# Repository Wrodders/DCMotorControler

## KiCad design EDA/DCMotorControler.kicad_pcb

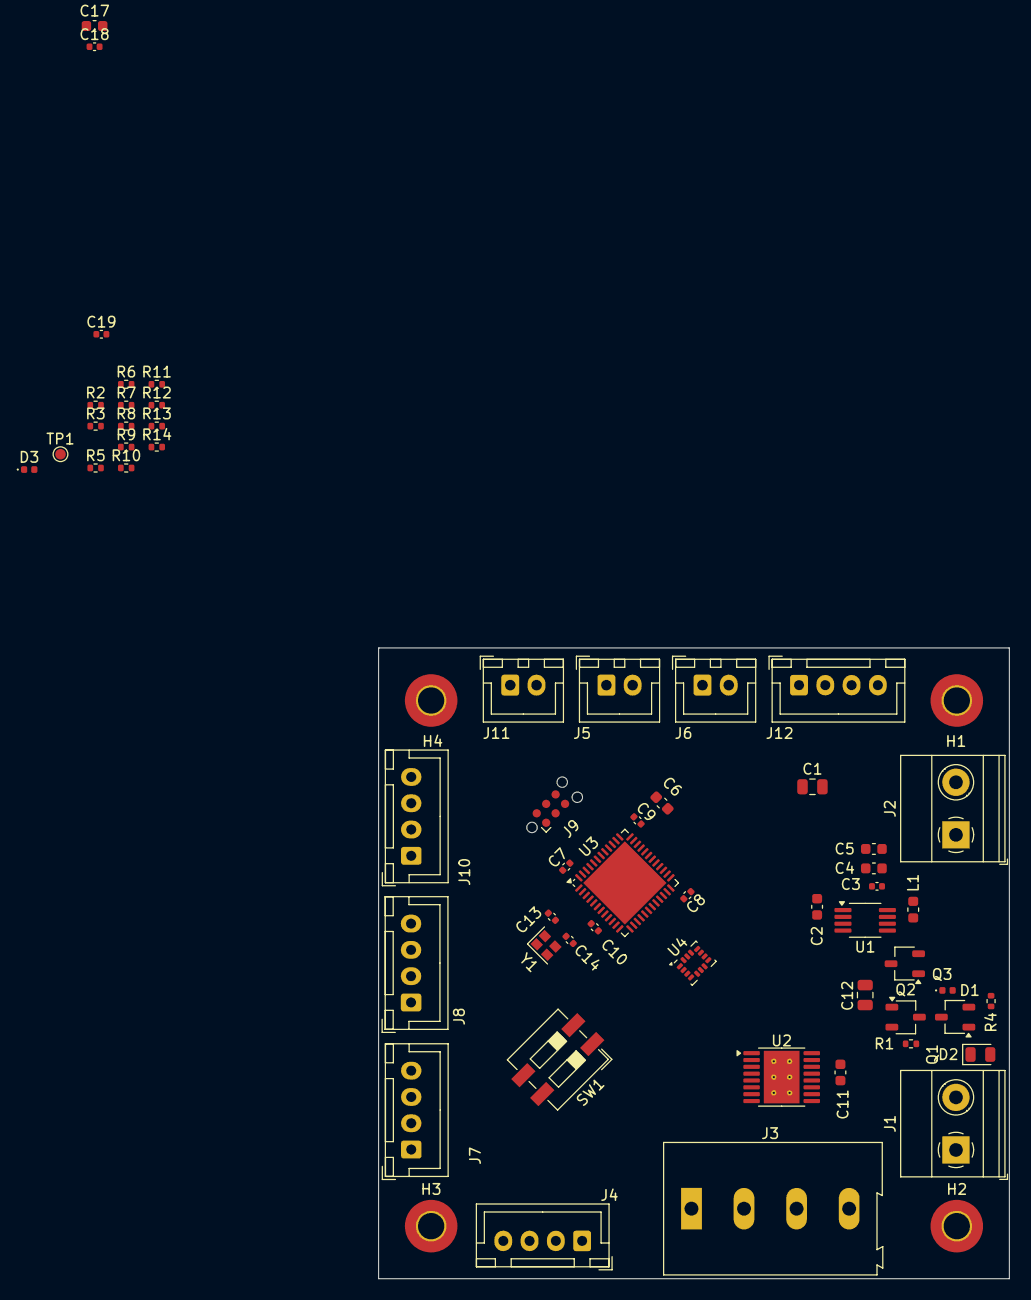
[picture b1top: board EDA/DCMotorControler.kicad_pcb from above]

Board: 2 copper layers, 60.0 x 60.0 mm, 61 parts (0 on the bottom side), 58 nets, no tracks yet.

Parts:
C1, C12: 47u; C_0805_2012Metric
C2, C4, C5, C11: 10u; C_0603_1608Metric
C3, C7, C8, C9, C10: 100n; C_0402_1005Metric
C6, C17: 4u7; C_0603_1608Metric
C13, C14, C19: 1u; C_0402_1005Metric
C18: 1uf; C_0402_1005Metric
D1: 16V; D_0402_1005Metric
D2: 1.5KExxA; D_0805_2012Metric
D3: LED_G; D_0402_1005Metric
H1, H2, H3, H4: MountingHole_Pad; MountingHole_2.5mm_Pad_TopBottom
J1, J2: Conn_01x02; TerminalBlock_Phoenix_MKDS-1,5-2_1x02_P5.00mm_Horizontal
J3: Conn_01x04; TerminalBlock_Altech_AK300-4_P5.00mm
J4, J7, J8, J10, J12: Conn_01x04; JST_XH_B4B-XH-A_1x04_P2.50mm_Vertical
J5, J6, J11: Conn_01x02; JST_XH_B2B-XH-A_1x02_P2.50mm_Vertical
J9: Conn_ARM_SWD_TagConnect_TC2030-NL; Tag-Connect_TC2030-IDC-NL_2x03_P1.27mm_Vertical
L1: 2u2; L_0603_1608Metric
Q1, Q2: AO3401A; TSOT-23
Q3: AO3400A; TSOT-23
R1, R2, R3, R14: 100k; R_0402_1005Metric
R4, R5, R7, R10, R11, R13: 10k; R_0402_1005Metric
R6, R8, R9: 0R; R_0402_1005Metric
R12: 1k; R_0402_1005Metric
SW1: SW_DIP_x02; SW_DIP_SPSTx02_Slide_6.7x6.64mm_W6.73mm_P2.54mm_LowProfile_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
TP1: TestPoint; TestPoint_Pad_D1.0mm
U1: TPS62162; MSOP-8_3x3mm_P0.65mm
U2: DRV8847PWP; HTSSOP-16-1EP_4.4x5mm_P0.65mm_EP3.4x5mm_Mask2.46x2.31mm_The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
U3: STM32F401CCUx; QFN-48-1EP_7x7mm_P0.5mm_EP5.6x5.6mm
U4: ICM-42670-P; LGA-14_3x2.5mm_P0.5mm_LayoutBorder3x4y
Y1: Crystal_GND24_Small; Crystal_SMD_2016-4Pin_2.0x1.6mm

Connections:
+3V3: C3.1, C4.1, C5.1, C6.1, C7.1, C8.1, C9.1, C10.1, J1.1, J8.1, J9.1 (VCC), J10.1, L1.2, R2.2, R3.2, R5.2, R11.2, R13.2, TP1.1, U3.1 (VBAT), U3.9 (VREF+), U3.24 (VDD), U3.36 (VDD), U3.48 (VDD), U4.5 (VDDIO), U4.8 (VDD)
/3V3_PG: Q3.2 (G), R3.1, U1.8 (PG)
/AOUT_L: J3.1, U2.2 (OUT1)
/AOUT_R: J3.3, U2.7 (OUT3)
/BOOT0: C19.1, R14.2, SW1.3, U3.44 (BOOT0)
/BOUT_L: J3.2, U2.4 (OUT2)
/BOUT_R: J3.4, U2.5 (OUT4)
/CLK0: C13.1, U3.5 (PH0), Y1.1
/CLK1: C14.1, U3.6 (PH1), Y1.3
/DEBUG_LED: R10.2, U3.2 (PC13)
/DEBUG_RX: J5.2, U3.31 (PA10)
/DEBUG_TX: J5.1, U3.30 (PA9)
/DRV_EN: R7.2, U2.1 (~SLEEP), U3.29 (PA8)
/ENC1A: J8.2, U3.40 (PB4)
/ENC1B: J8.3, U3.41 (PB5)
/ENC2A: J10.2, U3.42 (PB6)
/ENC2B: J10.3, U3.43 (PB7)
/I2C_SCL: J11.1, U3.45 (PB8)
/I2C_SDA: J11.2, U3.46 (PB9)
/IMU_CS: U3.38 (PA15), U4.12 (AP_CS)
/IMU_INT1: U3.3 (PC14), U4.4 (INT1/INT)
/IMU_INT2: U3.4 (PC15), U4.9 (INT2)
/NRST: C18.1, R9.2, R12.2, U3.7 (NRST)
/PWM1A: U2.16 (IN1), U3.10 (PA0)
/PWM1B: U2.15 (IN2), U3.11 (PA1)
/PWM2A: U2.9 (IN3), U3.12 (PA2)
/PWM2B: U2.10 (IN4), U3.13 (PA3)
/SPI1_CLK: J4.2, U3.15 (PA5), U4.13 (AP_SCL/AP_SCLK)
/SPI1_MISO: J4.3, U3.16 (PA6), U4.14 (AP_SDA/AP_SDIO/AP_SDI)
/SPI1_MOSI: J4.4, U3.17 (PA7), U4.1 (AP_SDO/AP_AD0)
/SPI2_CLK: J12.2, U3.26 (PB13)
/SPI2_MISO: J12.3, U3.27 (PB14)
/SPI2_MOSI: J12.4, U3.28 (PB15)
/SPI2_NSS: J12.1, U3.25 (PB12)
/STM.B0: J7.1, U3.18 (PB0)
/STM.B1: J7.2, U3.19 (PB1)
/STM.B2: J7.3, U3.20 (PB2)
/STM.B3: J7.4, U3.39 (PB3)
/SWCLK: J9.4 (SWCLK), U3.37 (PA14)
/SWDIO: J9.2 (SWDIO), U3.34 (PA13)
/USB_N: J6.2, U3.33 (PA12)
/USB_P: J6.1, U3.32 (PA11)
/VIN: D2.1 (A1), J2.2, Q1.1 (D)
/nFAULT_DRV: R5.1, U2.8 (~FAULT), U3.21 (PB10)
GND: C1.2, C2.2, C3.2, C4.2, C5.2, C6.2, C7.2, C8.2, C9.2, C10.2, C11.2, C12.2, C13.2, C14.2, C17.2, C18.2, C19.2, D2.2 (A2), D3.1 (K), H1.1, H2.1, H3.1, H4.1, J1.2, J2.1, J8.4, J9.5 (GND), J10.4, Q3.3 (S), R4.2, R6.2, R7.1, R8.2, R14.1, SW1.1, U1.1 (PGND), U1.4 (AGND), U1.5 (FB), U2.3 (ISEN12), U2.6 (ISEN34), U2.13 (GND), U2.17 (PPAD), U3.8 (VSSA), U3.23 (VSS), U3.35 (VSS), U3.47 (VSS), U3.49 (VSS), U4.6 (GND), U4.7 (FSYNC), Y1.2, Y1.4
unnamed: D1.2 (A), Q1.2 (G), R4.1
unnamed: D1.1 (K), Q1.3 (S), Q2.3 (S), R1.1
unnamed: D3.2 (A), R10.1
unnamed: J9.3 (~RESET), R9.1
unnamed: Q2.2 (G), Q3.1 (D), R1.2
unnamed: R11.1, R12.1, SW1.4
unnamed: R13.1, SW1.2
unnamed: L1.1, U1.7 (SW)
unnamed: R2.1, U1.6 (VOS)
unnamed: R6.1, U2.14 (MODE)
unnamed: R8.1, U2.11 (TRQ)
unnamed: C17.1, U3.22 (VCAP1)
VDC: C1.1, C2.1, C11.1, C12.1, Q2.1 (D), U1.2 (VIN), U1.3 (EN), U2.12 (VM)

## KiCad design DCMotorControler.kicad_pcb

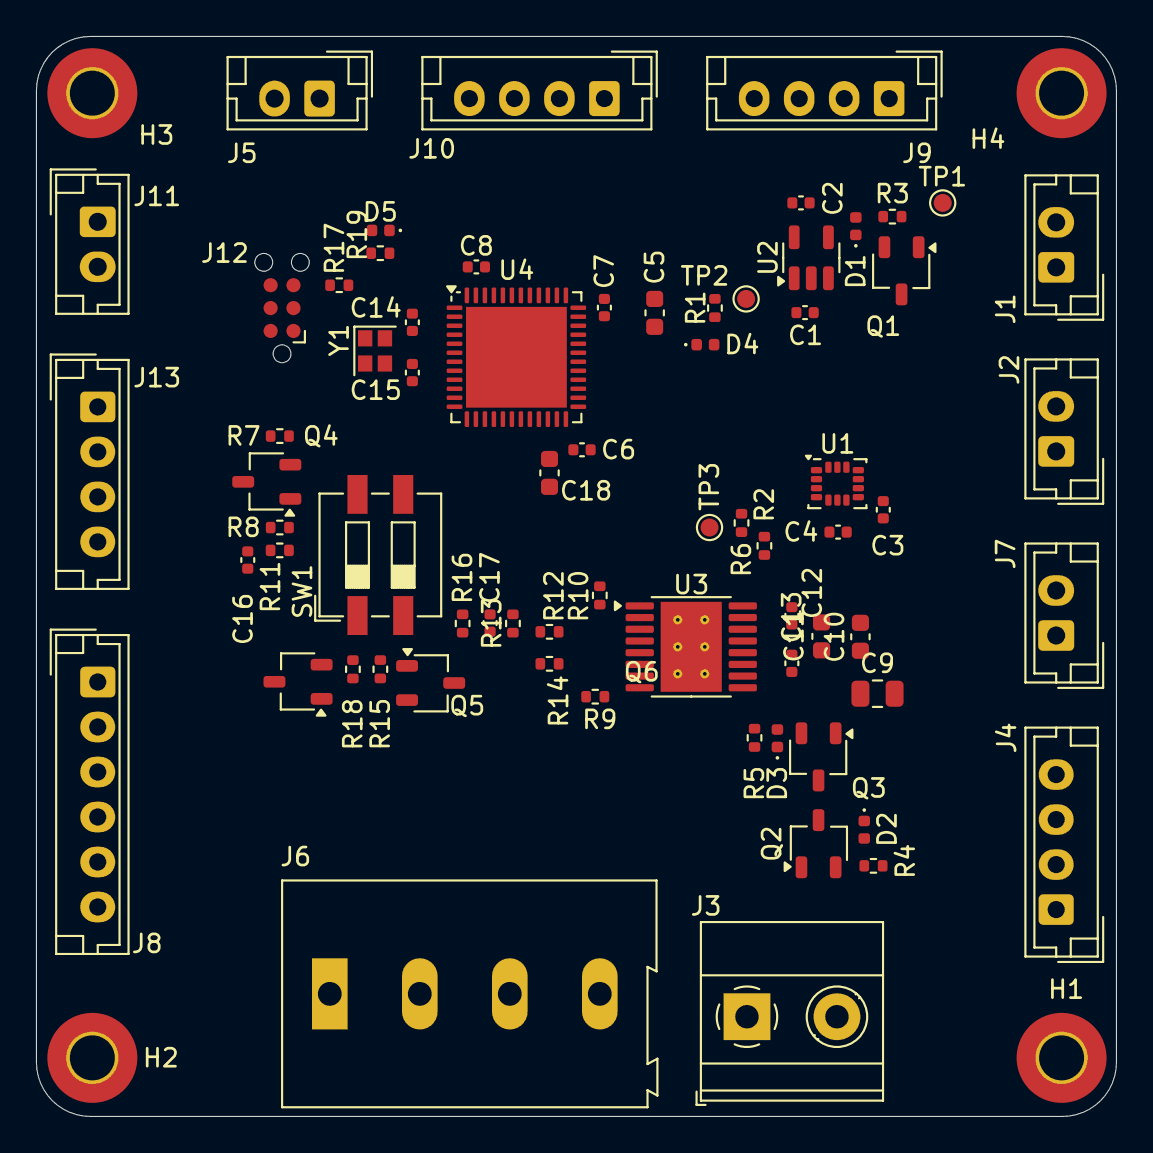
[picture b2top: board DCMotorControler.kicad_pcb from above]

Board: 2 copper layers, 60.0 x 60.0 mm, 74 parts (0 on the bottom side), 65 nets, no tracks yet.

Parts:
C1, C2, C14, C15, C17: 1u; C_0402_1005Metric
C3, C4, C6, C7, C8: 100n; C_0402_1005Metric
C5, C18: 4u7; C_0603_1608Metric
C9: 100u; C_0805_2012Metric
C10, C11: 10u; C_0603_1608Metric
C12: 2u2; C_0402_1005Metric
C13: 10n; C_0402_1005Metric
C16: 1uf; C_0402_1005Metric
D1, D2, D3: 16V; D_0402_1005Metric
D4, D5: GREEN; D_0402_1005Metric
H1, H2, H3, H4: MountingHole_Pad; MountingHole_2.5mm_Pad_TopBottom
J1, J2, J7: LOGIC Power; JST_EH_B2B-EH-A_1x02_P2.50mm_Vertical
J3: POWER; TerminalBlock_Phoenix_MKDS-1,5-2_1x02_P5.00mm_Horizontal
J4: SPI1; JST_EH_B4B-EH-A_1x04_P2.50mm_Vertical
J5: DEBUG SERIAL; JST_EH_B2B-EH-A_1x02_P2.50mm_Vertical
J6: MOTOR; TerminalBlock_Altech_AK300-4_P5.00mm
J8: GPIOS; JST_EH_B6B-EH-A_1x06_P2.50mm_Vertical
J9, J10: Conn_01x04; JST_EH_B4B-EH-A_1x04_P2.50mm_Vertical
J11: I2C1; JST_EH_B2B-EH-A_1x02_P2.50mm_Vertical
J12: Conn_ARM_SWD_TagConnect_TC2030-NL; Tag-Connect_TC2030-IDC-NL_2x03_P1.27mm_Vertical
J13: SPI2; JST_EH_B4B-EH-A_1x04_P2.50mm_Vertical
Q1, Q2, Q3, Q5: PMOS; TSOT-23
Q4, Q6: NMOS; TSOT-23
R1, R11: 1k; R_0402_1005Metric
R2, R15, R16, R18: 100k; R_0402_1005Metric
R3, R4, R5, R7, R8, R9, R10, R13, R19: 10k; R_0402_1005Metric
R6: 200k; R_0402_1005Metric
R12, R14: 80m; R_0402_1005Metric
R17: 0R; R_0402_1005Metric
SW1: SW_DIP_x02; SW_DIP_SPSTx02_Slide_6.7x6.64mm_W6.73mm_P2.54mm_LowProfile_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
TP1, TP2, TP3: TestPoint; TestPoint_Pad_D1.0mm
U1: ICM-42670-P; LGA-14_3x2.5mm_P0.5mm_LayoutBorder3x4y
U2: AP2112K-3.3; SOT-23-5
U3: DRV8833PWP; HTSSOP-16-1EP_4.4x5mm_P0.65mm_EP3.4x5mm_Mask2.46x2.31mm_The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
U4: STM32F401CCUx; QFN-48-1EP_7x7mm_P0.5mm_EP5.6x5.6mm
Y1: Crystal_GND24_Small; Crystal_SMD_2016-4Pin_2.0x1.6mm

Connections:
+3V3: C2.1, C3.1, C4.1, C5.1, C6.1, C7.1, C8.1, D3.2 (A), J2.1, J9.1, J10.1, J12.1 (VCC), Q3.2 (G), R1.2, R5.1, R8.2, R9.1, R13.2, TP2.1, U1.5 (VDDIO), U1.8 (VDD), U2.5 (VOUT), U4.1 (VBAT), U4.9 (VREF+), U4.24 (VDD), U4.36 (VDD), U4.48 (VDD)
/5VIN: C1.1, D1.1 (K), Q1.3 (S), U2.1 (VIN), U2.3 (EN)
/AOUT_L: J6.1, U3.2 (AOUT1)
/AOUT_R: J6.3, U3.7 (BOUT1)
/BOOT0: C17.1, Q5.3 (S), R16.2, SW1.3, U4.44 (BOOT0)
/BOOT_EN: J8.6, Q6.2 (G), R18.2
/BOUT_L: J6.2, U3.4 (AOUT2)
/BOUT_R: J6.4, U3.5 (BOUT2)
/CLK0: C14.1, U4.5 (PH0), Y1.1
/CLK1: C15.1, U4.6 (PH1), Y1.3
/DEBUG_LED: R19.2, U4.2 (PC13)
/DEBUG_RX: J5.2, U4.31 (PA10)
/DEBUG_TX: J5.1, U4.30 (PA9)
/DRV_EN: R10.1, U3.1 (~SLEEP), U4.29 (PA8)
/ENC1A: J9.2, U4.40 (PB4)
/ENC1B: J9.3, U4.41 (PB5)
/ENC2A: J10.2, U4.42 (PB6)
/ENC2B: J10.3, U4.43 (PB7)
/I2C_SCL: J11.1, U4.45 (PB8)
/I2C_SDA: J11.2, U4.46 (PB9)
/IMU_CS: U1.12 (AP_CS), U4.38 (PA15)
/IMU_INT1: U1.4 (INT1/INT), U4.3 (PC14)
/IMU_INT2: U1.9 (INT2), U4.4 (PC15)
/LVIN: J1.1, Q1.1 (D), TP1.1
/MVIN: J3.1, Q2.1 (D)
/NRST: R17.2, U4.7 (NRST)
/PWM1A: U3.16 (AIN1), U4.10 (PA0)
/PWM1B: U3.15 (AIN2), U4.11 (PA1)
/PWM2A: U3.9 (BIN1), U4.12 (PA2)
/PWM2B: U3.10 (BIN2), U4.13 (PA3)
/RST_STM: J8.5, Q4.2 (G), R7.2
/SPI1_CLK: J4.2, U1.13 (AP_SCL/AP_SCLK), U4.15 (PA5)
/SPI1_MISO: J4.3, U1.14 (AP_SDA/AP_SDIO/AP_SDI), U4.16 (PA6)
/SPI1_MOSI: J4.4, U1.1 (AP_SDO/AP_AD0), U4.17 (PA7)
/SPI2_CLK: J13.2, U4.26 (PB13)
/SPI2_MISO: J13.3, U4.27 (PB14)
/SPI2_MOSI: J13.4, U4.28 (PB15)
/SPI2_NSS: J13.1, U4.25 (PB12)
/STM.B0: J8.4, U4.18 (PB0)
/STM.B1: J8.3, U4.19 (PB1)
/STM.B2: J8.2, U4.20 (PB2)
/STM.B3: J8.1, U4.39 (PB3)
/SWCLK: J12.4 (SWCLK), U4.37 (PA14)
/SWDIO: J12.2 (SWDIO), U4.34 (PA13)
/USB_N: J7.2, U4.33 (PA12)
/USB_P: J7.1, U4.32 (PA11)
/VBATMON: R2.2, R6.1, TP3.1, U4.14 (PA4)
/nFAULT_DRV: R9.2, U3.8 (~FAULT), U4.21 (PB10)
GND: C1.2, C2.2, C3.2, C4.2, C5.2, C6.2, C7.2, C8.2, C9.2, C10.2, C11.2, C12.2, C14.2, C15.2, C16.2, C17.2, C18.2, D4.1 (K), D5.1 (K), H1.1, H2.1, H3.1, H4.1, J1.2, J2.2, J3.2, J9.4, J10.4, J12.5 (GND), Q4.3 (S), Q6.3 (S), R3.2, R4.2, R5.2, R6.2, R7.1, R10.2, R12.2, R14.2, R16.1, R18.1, SW1.1, U1.6 (GND), U1.7 (FSYNC), U2.2 (GND), U3.13 (GND), U3.17 (GND), U4.8 (VSSA), U4.23 (VSS), U4.35 (VSS), U4.47 (VSS), U4.49 (VSS), Y1.2, Y1.4
unnamed: C16.1, R11.2
unnamed: D1.2 (A), Q1.2 (G), R3.1
unnamed: D2.2 (A), Q2.2 (G), R4.1
unnamed: D2.1 (K), D3.1 (K), Q2.3 (S), Q3.3 (S)
unnamed: D4.2 (A), R1.1
unnamed: D5.2 (A), R19.1
unnamed: J12.3 (~RESET), R17.1
unnamed: Q4.1 (D), R8.1, R11.1, SW1.4
unnamed: Q5.1 (D), R13.1, R15.2, SW1.2
unnamed: Q5.2 (G), Q6.1 (D), R15.1
unnamed: R12.1, U3.3 (AISEN)
unnamed: R14.1, U3.6 (BISEN)
unnamed: C13.2, U3.11 (VCP)
unnamed: C12.1, U3.14 (VINT)
unnamed: C18.1, U4.22 (VCAP1)
VDC: C9.1, C10.1, C11.1, C13.1, Q3.1 (D), R2.1, U3.12 (VM)

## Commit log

2024-04-22 initialLaypout
